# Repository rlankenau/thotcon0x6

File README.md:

thotcon0x6
==========

Thotcon 0x6 badge stuff.

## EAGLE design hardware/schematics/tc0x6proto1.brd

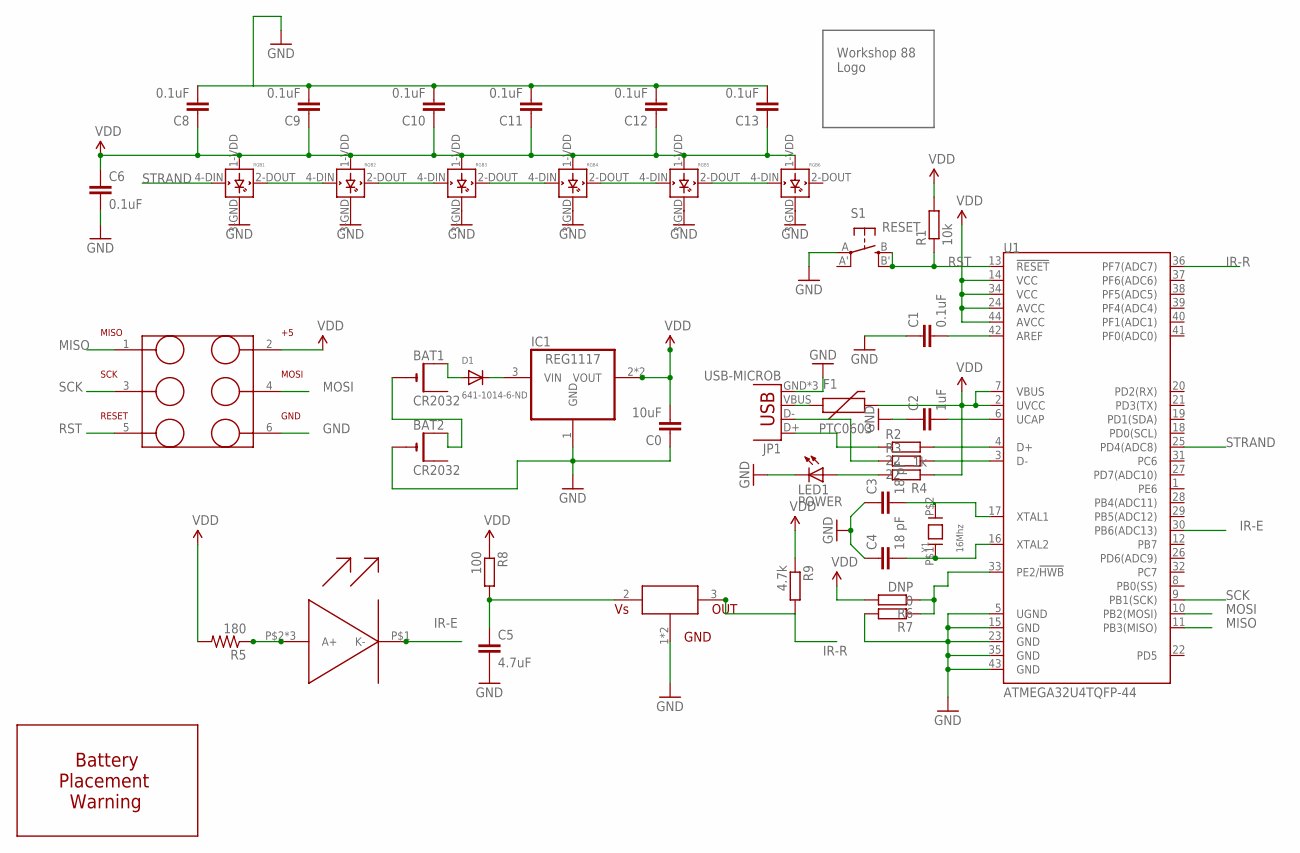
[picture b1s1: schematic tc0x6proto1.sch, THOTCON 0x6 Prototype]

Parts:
BAT1, BAT2: CR2032; CR2032-SMD
C0: 10uF; C0603
C1, C8, C9, C10, C11, C12, C13: 0.1uF; C0603
C2: 1uF; C0603
C3, C4: 18 pF; C0603
C5: 4.7uF; C0603
C6: 0.1uF; 0603-CAP
D1: 641-1014-6-ND; SMADIODE
F1: PTC0603; 0603
IC1: REG1117; SOT223
JP1: USB-MICROB
LED1: POWER; CHIPLED_1206
R1: 10k; R0603
R2, R3: 22; R0603
R4: 1k; R0603
R5: 180; 0603-RES
R6: DNP; R0603
R7: 0; R0603
R8: 100; R0603
R9: 4.7k; R0603
RGB1, RGB2, RGB3, RGB4, RGB5, RGB6: WS2812B
S1: RESET; EVQ-Q2
U1: ATMEGA32U4TQFP-44; TQFP44
U2: TSMP77000; TSMP77000TT
U3: SFH4259S; POWER_TOPLED_WITH_LENS
U$1: W88LOGO; W88-LOGO
U$4: AVR-TAG-CONNECTSNAP-ON; TC2030-MCP
U$5: BATTERY_WARNING; BATTERY_PLACEMENT_WARN
Y1: 16Mhz; SMD5MMX3.2MM

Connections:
BAT_BAT: BAT1.-, BAT2.+$1 (+)
GND: BAT2.-, C0.1, C1.1, C2.1, C3.1, C4.1, C5.2, C6.2, C8.2, C9.2, C10.2, C11.2, C12.2, C13.2, IC1.1 (GND), JP1.GND, JP1.MT1 (GND), JP1.MT2 (GND), LED1.C, R7.2, RGB1.3-GND (GND), RGB2.3-GND (GND), RGB3.3-GND (GND), RGB4.3-GND (GND), RGB5.3-GND (GND), RGB6.3-GND (GND), S1.A, U1.5 (UGND), U1.15 (GND), U1.23 (GND), U1.35 (GND), U1.43 (GND), U2.1 (GND), U2.4 (GND), U$4.6 (GND)
IR-E: U1.30 (PB6(ADC13)), U3.P$1 (K-)
IR-R: R9.2, U1.36 (PF7(ADC7)), U2.3 (OUT)
MISO: U1.11 (PB3(MISO)), U$4.1 (MISO)
MOSI: U1.10 (PB2(MOSI)), U$4.4 (MOSI)
unnamed: C5.1, R8.2, U2.2 (VDD)
unnamed: R3.2, U1.3 (D-)
unnamed: R6.1, R7.1, U1.33 (PE2/!HWB)
unnamed: JP1.D+, R2.1
unnamed: C1.2, U1.42 (AREF)
unnamed: R2.2, U1.4 (D+)
unnamed: JP1.D-, R3.1
unnamed: LED1.A, R4.2
unnamed: C2.2, U1.6 (UCAP)
unnamed: C3.2, U1.17 (XTAL1), Y1.P$2 (2)
unnamed: C4.2, U1.16 (XTAL2), Y1.P$1 (1)
unnamed: R5.1, U3.P$2 (A+), U3.P$3 (A+), U3.P$4 (A+)
unnamed: F1.1, JP1.VBUS
RST: R1.1, S1.B (S), S1.B' (S1), U1.13 (!RESET), U$4.5 (RESET)
SCK: U1.9 (PB1(SCK)), U$4.3 (SCK)
STRAND: RGB1.4-DIN (DIN), U1.25 (PD4(ADC8))
STRAND_1_2: RGB1.2-DOUT (DOUT), RGB2.4-DIN (DIN)
STRAND_2_3: RGB2.2-DOUT (DOUT), RGB3.4-DIN (DIN)
STRAND_3_4: RGB3.2-DOUT (DOUT), RGB4.4-DIN (DIN)
STRAND_4_5: RGB4.2-DOUT (DOUT), RGB5.4-DIN (DIN)
STRAND_5_6: RGB5.2-DOUT (DOUT), RGB6.4-DIN (DIN)
VBAT: BAT1.+$1 (+), D1.A
VBAT_RECT: D1.C, IC1.3 (VIN)
VDD: C0.2, C6.1, C8.1, C9.1, C10.1, C11.1, C12.1, C13.1, F1.2, IC1.2 (VOUT), IC1.4 (VOUT), R1.2, R4.1, R5.2, R6.2, R8.1, R9.1, RGB1.1-VDD (VDD), RGB2.1-VDD (VDD), RGB3.1-VDD (VDD), RGB4.1-VDD (VDD), RGB5.1-VDD (VDD), RGB6.1-VDD (VDD), U1.2 (UVCC), U1.7 (VBUS), U1.14 (VCC), U1.24 (AVCC), U1.34 (VCC), U1.44 (AVCC), U$4.2 (VCC)

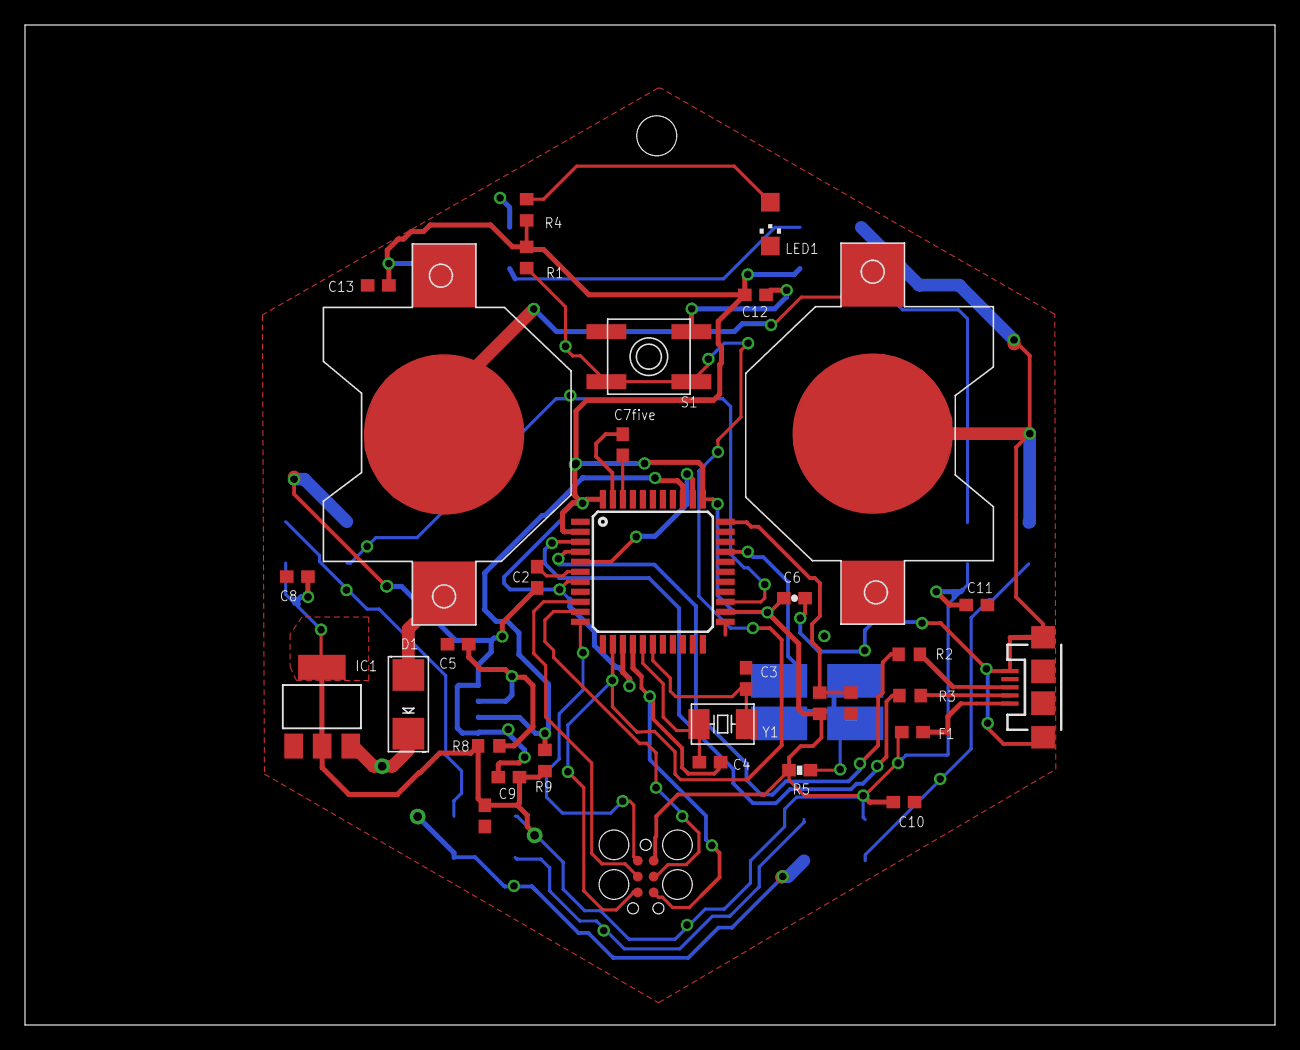
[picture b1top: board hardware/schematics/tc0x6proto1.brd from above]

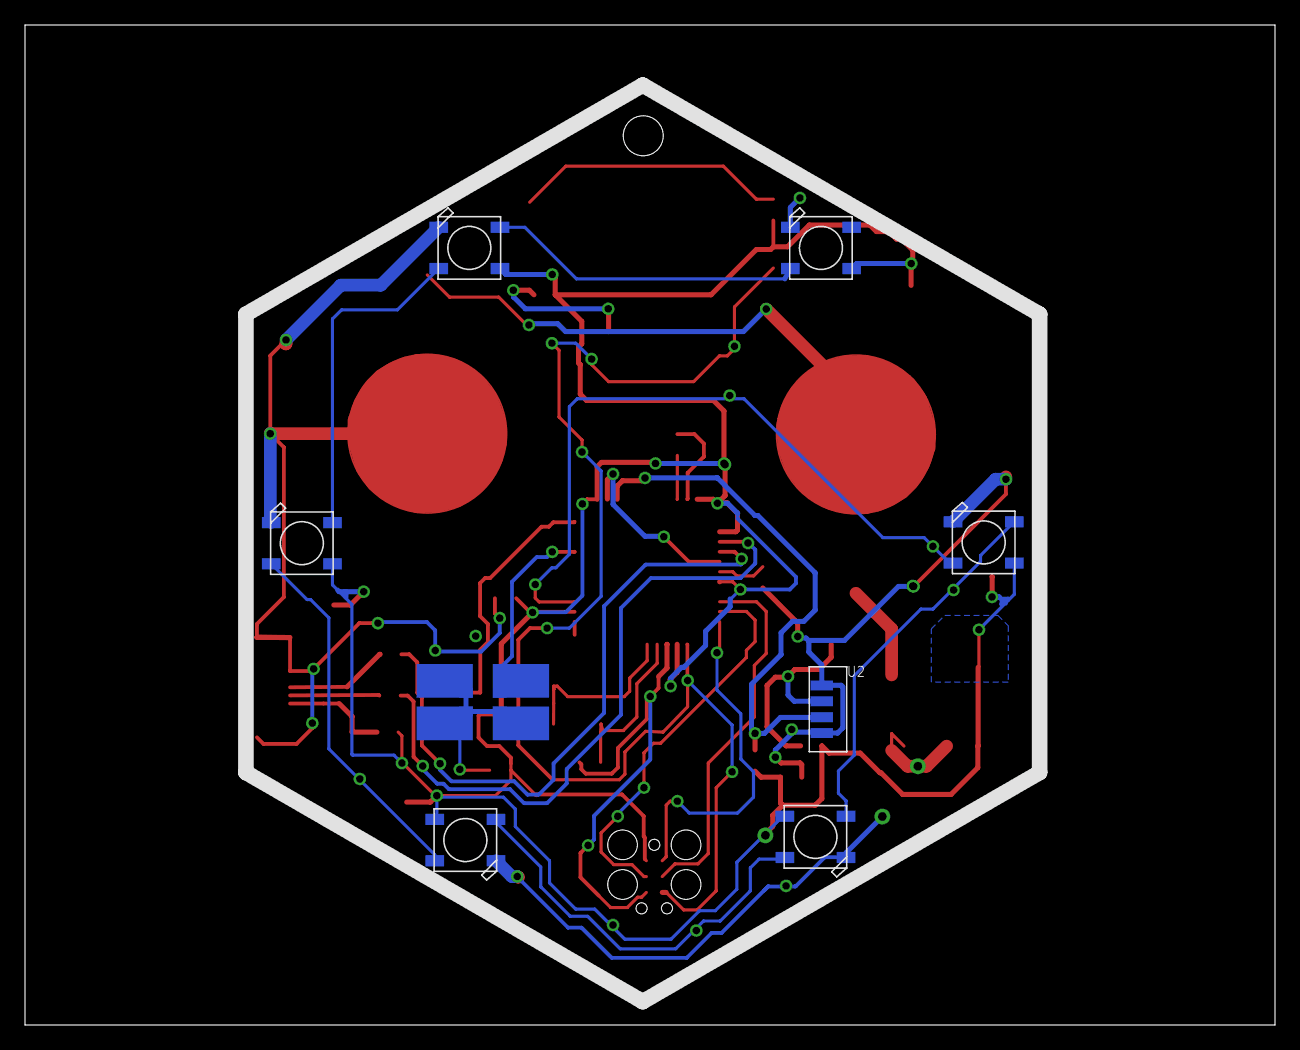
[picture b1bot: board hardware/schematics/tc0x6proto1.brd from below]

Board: 2 copper layers, 100.0 x 80.0 mm, 43 parts (8 on the bottom side), 30 nets.

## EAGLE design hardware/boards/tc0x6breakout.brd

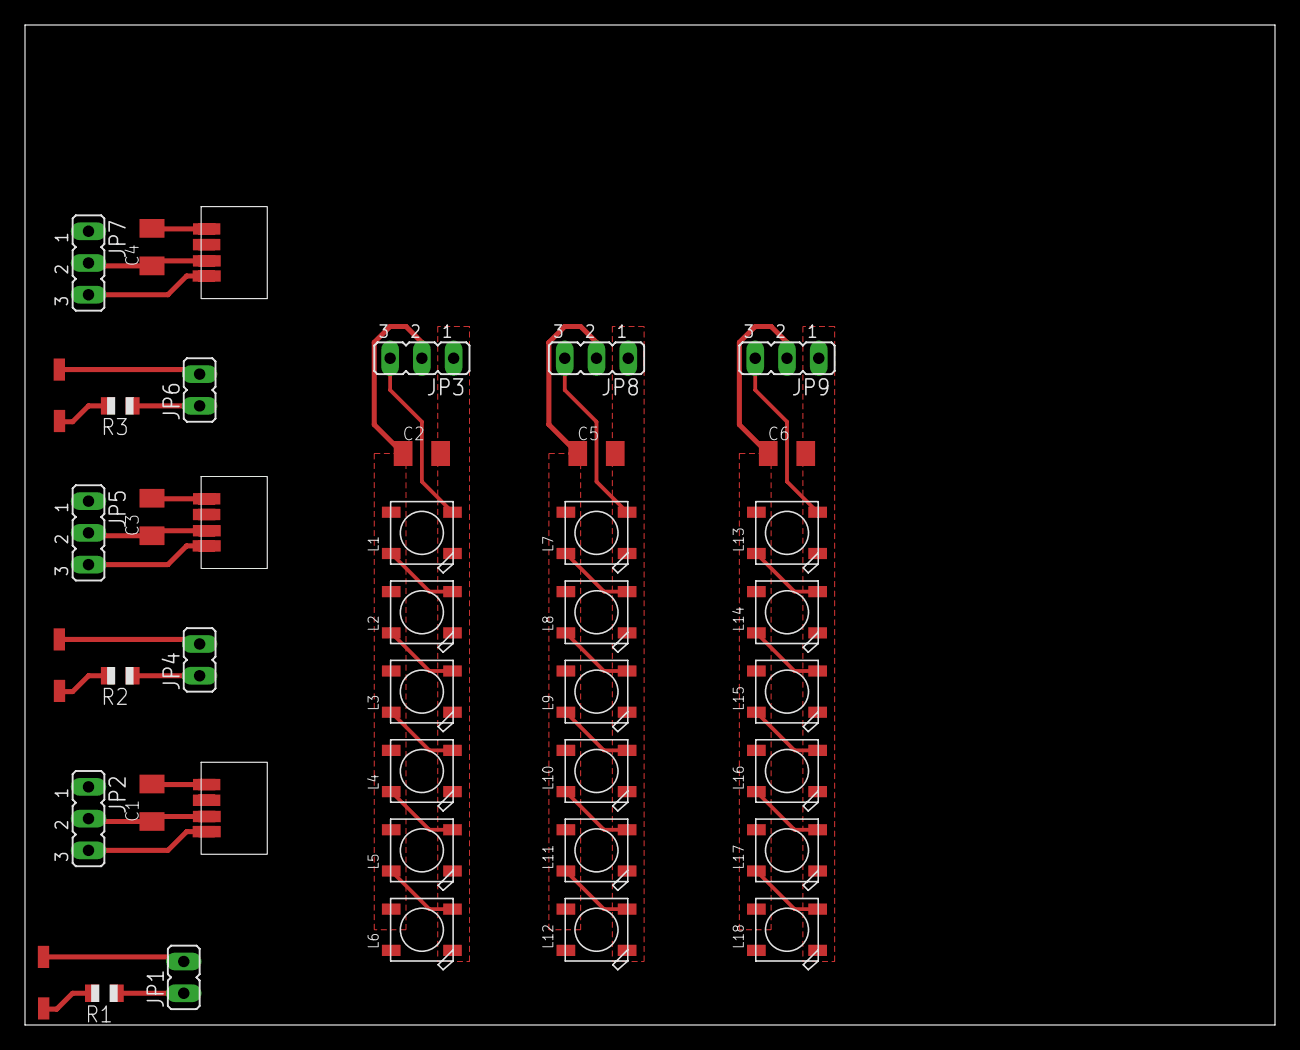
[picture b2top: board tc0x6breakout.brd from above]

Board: 2 copper layers, 100.0 x 80.0 mm, 42 parts (0 on the bottom side), 42 nets.

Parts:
C1, C2, C3, C4, C5, C6: C1206K
JP1, JP4, JP6: V O; JP1
JP2, JP5, JP7: O V G; JP2
JP3, JP8, JP9: I V G; JP2
L1, L2, L3, L4, L5, L6, L7, L8, L9, L10, L11, L12, L13, L14, L15, L16, L17, L18: WS2812B
R1, R2, R3: 150; R0805
U$1, U$3, U$5: TSML10X0; TSML10X0SMD
U$2, U$4, U$6: TSOP362; TSOP362SMD

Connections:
DIO: JP3.3, L1.4-DIN
DIO1: JP8.3, L7.4-DIN
DIO2: JP9.3, L13.4-DIN
GND: C2.2, JP3.1, L1.3-GND, L2.3-GND, L3.3-GND, L4.3-GND, L5.3-GND, L6.3-GND
GND1: C5.2, JP8.1, L7.3-GND, L8.3-GND, L9.3-GND, L10.3-GND, L11.3-GND, L12.3-GND
GND2: C6.2, JP9.1, L13.3-GND, L14.3-GND, L15.3-GND, L16.3-GND, L17.3-GND, L18.3-GND
unnamed: JP1.1, R1.1
unnamed: JP1.2, U$1.P$A
unnamed: R1.2, U$1.P$C
unnamed: C1.1, JP2.2, U$2.P$VDD, U$2.P$VDD2
unnamed: C1.2, JP2.1, U$2.P$GND, U$2.P$GND2
unnamed: L2.2-DOUT, L3.4-DIN
unnamed: JP2.3, U$2.P$OUT, U$2.P$OUT2
unnamed: L3.2-DOUT, L4.4-DIN
unnamed: L4.2-DOUT, L5.4-DIN
unnamed: L1.2-DOUT, L2.4-DIN
unnamed: L5.2-DOUT, L6.4-DIN
unnamed: JP4.1, R2.1
unnamed: JP4.2, U$3.P$A
unnamed: R2.2, U$3.P$C
unnamed: C3.1, JP5.2, U$4.P$VDD, U$4.P$VDD2
unnamed: C3.2, JP5.1, U$4.P$GND, U$4.P$GND2
unnamed: JP5.3, U$4.P$OUT, U$4.P$OUT2
unnamed: JP6.1, R3.1
unnamed: JP6.2, U$5.P$A
unnamed: R3.2, U$5.P$C
unnamed: C4.1, JP7.2, U$6.P$VDD, U$6.P$VDD2
unnamed: C4.2, JP7.1, U$6.P$GND, U$6.P$GND2
unnamed: JP7.3, U$6.P$OUT, U$6.P$OUT2
unnamed: L7.2-DOUT, L8.4-DIN
unnamed: L8.2-DOUT, L9.4-DIN
unnamed: L9.2-DOUT, L10.4-DIN
unnamed: L11.2-DOUT, L12.4-DIN
unnamed: L10.2-DOUT, L11.4-DIN
unnamed: L13.2-DOUT, L14.4-DIN
unnamed: L14.2-DOUT, L15.4-DIN
unnamed: L15.2-DOUT, L16.4-DIN
unnamed: L17.2-DOUT, L18.4-DIN
unnamed: L16.2-DOUT, L17.4-DIN
VDD: C2.1, JP3.2, L1.1-VDD, L2.1-VDD, L3.1-VDD, L4.1-VDD, L5.1-VDD, L6.1-VDD
VDD1: C5.1, JP8.2, L7.1-VDD, L8.1-VDD, L9.1-VDD, L10.1-VDD, L11.1-VDD, L12.1-VDD
VDD2: C6.1, JP9.2, L13.1-VDD, L14.1-VDD, L15.1-VDD, L16.1-VDD, L17.1-VDD, L18.1-VDD

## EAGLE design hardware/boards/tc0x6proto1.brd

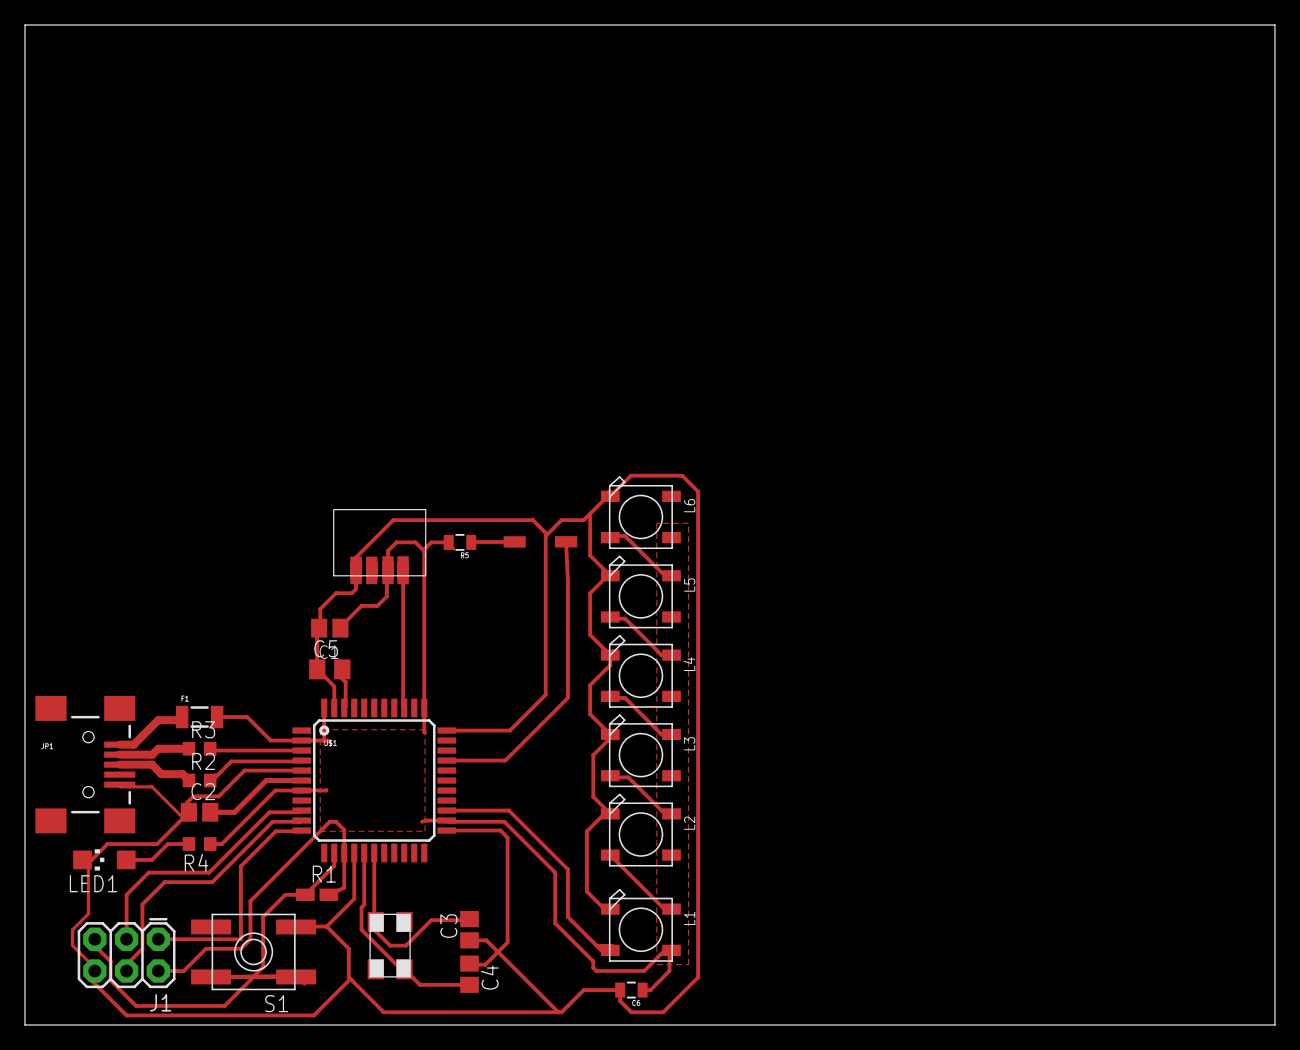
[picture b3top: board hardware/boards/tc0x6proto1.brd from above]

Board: 2 copper layers, 100.0 x 80.0 mm, 26 parts (0 on the bottom side), 25 nets.

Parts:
C1: 0.1uF; C0805K
C2: 1uF; C0805
C3, C4: 18 pF; C0805
C5: 0.1uF; C0805
C6: 0.1uF; 0805
F1: PTCSMD; PTC-1206
J1: AVR_SPI; 2X3
JP1: USBSMD; USB-MINIB
L1, L2, L3, L4, L5, L6: WS2812B
LED1: POWER; CHIPLED_1206
R1: 10k; R0805W
R2, R3: 22; R0603
R4: 1k; R0603
R5: 180; 0805
S1: RESET; EVQ-Q2
U$1: ATMEGA32U4TQFP-44; TQFP44
U$2: TSML10X0; TSML10X0SMD
U$3: TSOP362; TSOP362SMD
Y1: 16Mhz; 5X3.2MM

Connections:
GND: C1.1, C2.1, C3.1, C4.1, C5.2, C6.2, J1.6, JP1.GND, L1.3-GND, L2.3-GND, L3.3-GND, L4.3-GND, L5.3-GND, L6.3-GND, LED1.C, S1.A, U$1.5, U$1.15, U$1.23, U$1.33, U$1.35, U$1.43, U$3.P$GND, U$3.P$GND2
IR-E: U$1.30, U$2.P$A
IR-R: U$1.36, U$3.P$OUT, U$3.P$OUT2
MISO: J1.1, U$1.11
MOSI: J1.4, U$1.10
unnamed: R3.2, U$1.3
unnamed: L1.2-DOUT, L2.4-DIN
unnamed: L2.2-DOUT, L3.4-DIN
unnamed: L3.2-DOUT, L4.4-DIN
unnamed: L4.2-DOUT, L5.4-DIN
unnamed: L5.2-DOUT, L6.4-DIN
unnamed: JP1.D+, R2.1
unnamed: C1.2, U$1.42
unnamed: R2.2, U$1.4
unnamed: JP1.D-, R3.1
unnamed: LED1.A, R4.2
unnamed: C2.2, U$1.6
unnamed: C3.2, U$1.17, Y1.3
unnamed: C4.2, U$1.16, Y1.1
unnamed: R5.1, U$2.P$C
unnamed: F1.1, JP1.VBUS
RST: J1.5, R1.1, S1.B, S1.B', U$1.13
SCK: J1.3, U$1.9
STRAND: L1.4-DIN, U$1.25
VDD: C5.1, C6.1, F1.2, J1.2, L1.1-VDD, L2.1-VDD, L3.1-VDD, L4.1-VDD, L5.1-VDD, L6.1-VDD, R1.2, R4.1, R5.2, U$1.2, U$1.7, U$1.14, U$1.24, U$1.34, U$1.44, U$3.P$VDD, U$3.P$VDD2

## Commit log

2015-03-03 initial push from Rudy
    hardware work to date, working BoM, single side eagles, art, datasheets
    and a little code
2015-03-09 hardware updates
    eagles and negatives
2015-03-09 Create IR-badge.ino
    School me on git later.
2015-03-09 Use IR-Comm-Badge.ino Image it is the the working copy
2015-03-10 Use IR-Comm-Badge.ino significant updates now intagrated image with ir recieve and transmit. Using the same parts as production badge
2015-03-10 stencil files
    various files for etching solder mask stencils
2015-03-10 Some minor tweaks added notes for where to add nixie updates added a delay that should be a little more random to hit signal one or 2 to change blink pattern
2015-03-20 art for hardware
2015-03-24 Updated prototype with art, LDO, and batteries.
2015-03-24 Added gerbers for prototype review.
2015-03-25 Fixed incorrect layout for voltage regulator, changed to 0603 packaging
2015-03-26 Updated board with tag connect and ground pour. Battery holders still need to be changed out for better parts.
2015-04-02 Added diode, fixed battery hookup direction, added battery warning.
2015-04-06 Modified bottom silk. Added gerbers for initial quote.
2015-04-07 Updated board with TSMP77000 rather than TSOP362
2015-04-22 Fixed font size, replaced xtal, cleaned up bottom ground trace.
2015-04-23 Added jumper for USB boot select.
2015-04-23 Moved power supply filter capacitor
2015-04-28 Added LED caps
2015-04-30 added strandtest_emitter sketch
2015-05-03 Added code to do Serial debugging, changed IR_E to active-low, added pullup code for IR_R.
2015-05-05 For programming over USB, the Arduino IDE opens and closes the serial port to force a reset. Unfortunately, this also causes the board to re-enumerate and possible get a new device. Added some script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
2015-05-05 Added sleep and retry. Programming is repeatable now.
2015-05-06 boot sequence
    playing around with some boot paramaters and animations.
2015-05-06 Revert "boot sequence"
    This reverts commit 990b869b8c648723e8cab18e1544e45a2ad0623f.
2015-05-06 fastLED swap
    changed lighting library to FastLED
2015-05-06 switched to FastLED
    basic serial controlled dump of patterns WIP -R-
2015-05-06 Added header for EEPROM layout.
2015-05-07 Add initial run of final sketch
2015-05-07 added eprom2string routine that reads from EEPROM and returns null terminated string
2015-05-07 library
2015-05-07 uber 3ll37 hand made ascii
2015-05-07 bbs wip
2015-05-07 Updated programming scripts, added display functions.
2015-05-07 Added eeprom.bin with basic outline of EEPROM. Please edit this with a hex editor and re-export eeprom.hex as 8-bit Intel hex, 32 bytes per line.
2015-05-07 Added w88 display code, set_led util function, updated eeprom with w88 content.
2015-05-07 Fix compiler errors from merge.
2015-05-07 Modify location of avrdude for MacOSX
2015-05-07 should identify as THOTCON Badge0x6, needs to be tested
2015-05-08 Updated doc for EEPROM layout.
2015-05-08 Added bin version of bootloader.
2015-05-08 Fixed checksums on bootloader.hex
2015-05-08 Added hex for red/blue, root, oper.
2015-05-08 Updated OPER badge to flash SOS
2015-05-08 Updated hex for oper badge pattern
2015-05-08 added VIP display.
2015-05-08 Added hacker hex
2015-05-08 Added more display code.
2015-05-08 Oops, 2500 baud...
2015-05-08 Fixed flags so they actually correspond to the right badge types.
2015-05-08 changes from last night. -R-
2015-05-09 more console updates
2015-05-10 fixed a few types to try to get the eeprom code working better.
2015-05-10 fixed some flow controll issues
2015-05-10 tweaks -R-
2015-05-10 Fixed ROOT pattern. Needed to cast 0xF8 to a char to prevent sign-extension during comparision
2015-05-10 Fixed display code and eeprom.
2015-05-10 Added RED/BLUE flags to burn.sh for testing.
2015-05-10 dumps IR from the reciever
2015-05-10 Added peek/poke interface
2015-05-10 minor changes
2015-05-10 Parsing of display address and sub value
2015-05-10 removed merge comments
2015-05-10 Patch up merge problem
2015-05-10 Put lower and upper limits on substitute
2015-05-10 Integrated BBS and LED display
2015-05-10 Added code to transmit 4 bytes over IR.
2015-05-10 Added checksum to IR data
2015-05-10 ir shark added to bbs
2015-05-11 Added IR receiver code.
2015-05-11 Added random flash.
2015-05-11 Increased EEPROM entropy.
2015-05-11 sleep code, needs review
2015-05-11 save vs down
2015-05-11 various mergers and acquisitions
2015-05-12 Flashing stuff.
2015-05-12 disable safe mode in the USB burn because the fuses don't read correctly even though they're correct.
2015-05-12 Final stuff to burn
2015-05-12 Added final sketch
2015-05-12 added terminators to eeprom.
2015-05-12 removed type from burn.sh
2015-05-13 Removed Poof/IRPlay, etc.
2015-05-13 program.pl for usbtiny, removed port issue.Resourceo
2015-05-13 timing update
2015-05-13 libs
2015-05-13 Compile for Rudy's fixes.
2015-05-14 Changed INPUT_PULLUP to INPUT

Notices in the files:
parts and their libraries:
SparkFun-DigitalIC: Licensing: Creative Commons ShareAlike 4.0 International - https://creativecommons.org/licenses/by-sa/4.0
w88: ©2009 ROFA.cz - modified and updated by Robert Darlington ‹rdarlington@gmail.com›
